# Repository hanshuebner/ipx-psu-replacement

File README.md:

# Sun SPARCstation IPC/IPX replacement power supply

I've got tired of unsuccessfully trying to repair the APS-02 power
supply that is built into Sun's SPARCstation IPC and IPX workstations,
so I designed this replacement.  It uses two encapsulated power
supplies and a MAX8215 power supply monitoring chip to generate the
SENS signal.

Here's a picture of my version 1 build.  It has the base load
resistors bodged on.  The layout has been revised since:

Several parts out of the original PSU board are reused and need to be
desoldered:

|Ref |Qnty|Value    |Notes                                         |
|----|----|---------|----------------------------------------------|
|F1  |1   |3.15A T  |Fuse + fuse holder                            |
|J1  |1   |L        |Power input (3 pin, middle pin not connected) |
|J2  |1   |AC IN    |Power from IEC input (1 pin)                  |
|J5  |1   |AC OUT   |Power to IEC output (1 pin)                   |
|J12 |1   |Fan      |Power to fan (2 pin)                          |
|K1  |1   |DH2U TV3 |IEC output relay                              |
|    |1   |         |Cable harness including floppy connector      |

Another couple of parts need to be bought

|Ref           |Qnty|Value      |Description                                                                 |
|--------------|----|-----------|----------------------------------------------------------------------------|
|U1            |1   |74HCT11D   |Triple 3-input AND, SO-14                                                   |
|U2            |1   |MAX8215CSD |Voltage Monitor IC, SO-14                                                   |
|D1            |1   |PMEG2010ER |20V 1A Planar Schottky barrier rectifier, SOD-123                           |
|C1, C2        |2   |100nF      |Capacitor bipolar SMD 0603                                                  |
|C3            |1   |1µF        |Capacitor bipolar SMD 0603                                                  |
|R1, R2, R3, R4|4   |680kΩ      |Resistor SMD 0603                                                           |
|R5, R6        |2   |120Ω       |Resistor radial 5W, 20mmx9mmx9mm, 25mm pitch                                |
|PS1           |1   |IRM-60-5   |MeanWell IRM-60-5 50 Watt AC/DC power supply, 5V, 10A                       |
|PS2           |1   |RACM30-12DK|RECOM RACM30-12DK/277 30 Watt Dual Output AC/DC power supply, ±12V, ±1250mA |

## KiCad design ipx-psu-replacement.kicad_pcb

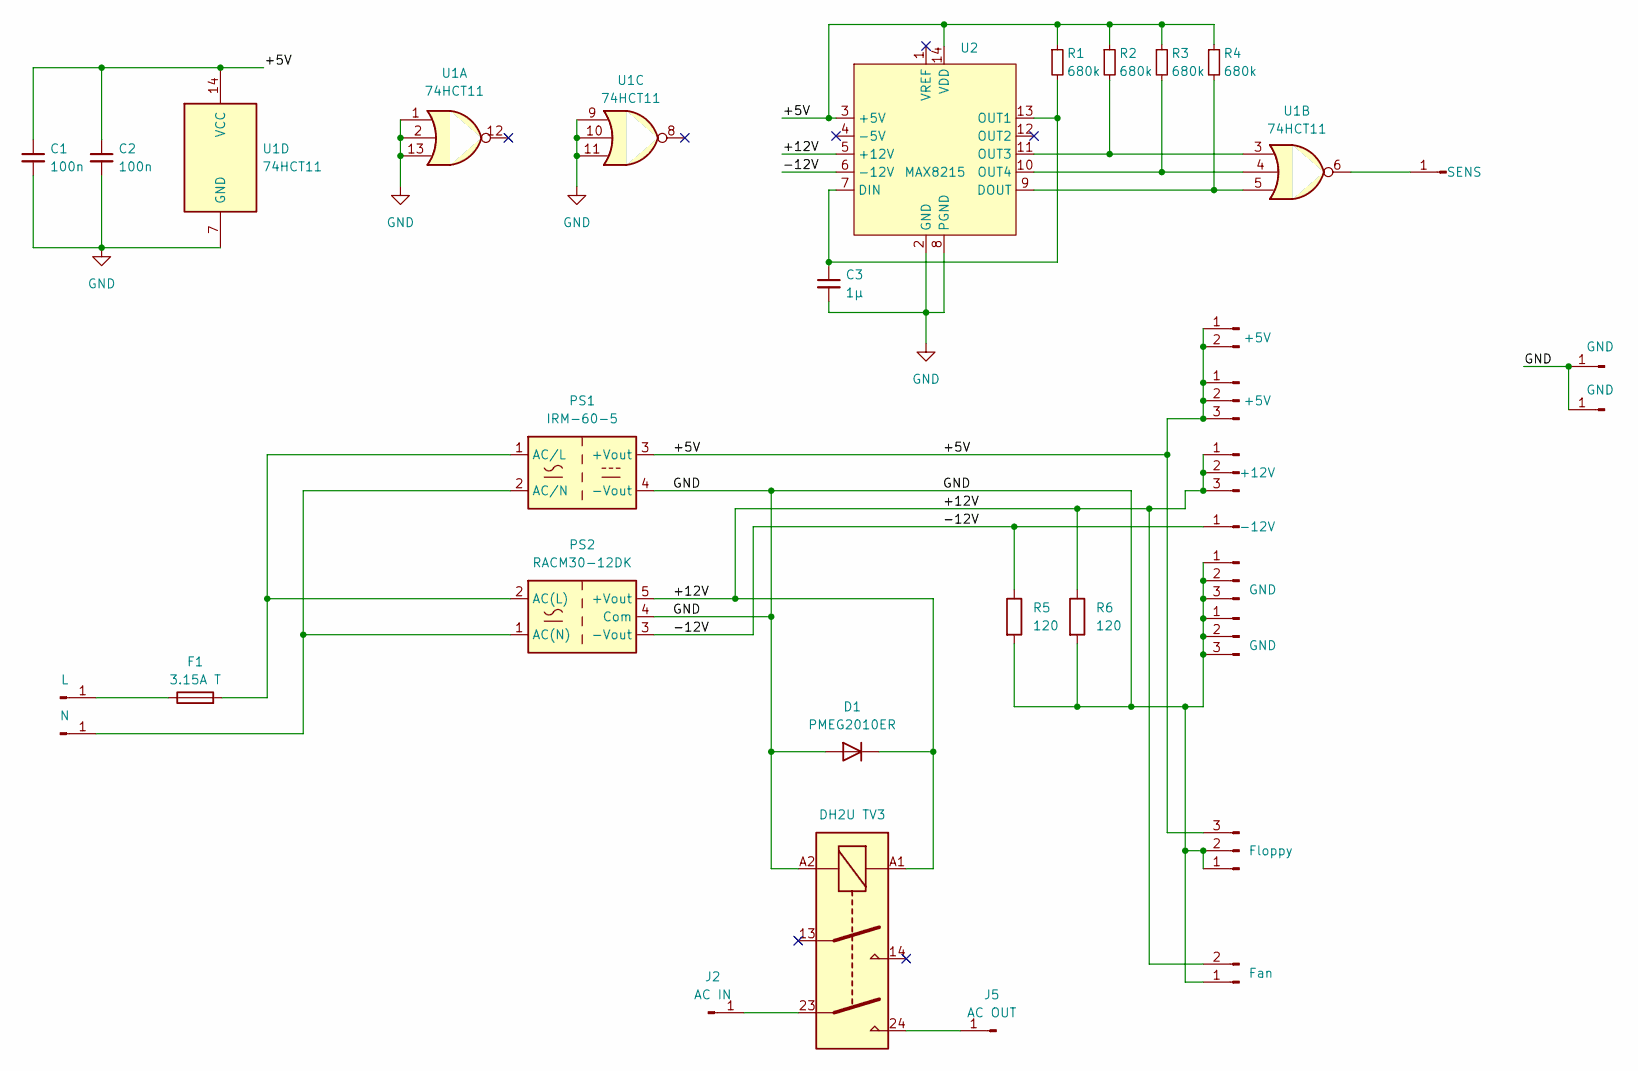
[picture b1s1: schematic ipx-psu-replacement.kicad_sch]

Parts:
C1, C2: 100n; C_0603_1608Metric_Pad1.08x0.95mm_HandSolder
C3: 1µ; C_0603_1608Metric_Pad1.08x0.95mm_HandSolder
D1: PMEG2010ER; D_SOD-123
F1: 3.15A T; Fuseholder_Clip-5x20mm_Littelfuse_111_Inline_P20.00x5.00mm_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
J1: L; SolderWire-1.5sqmm_1x01_D1.7mm_OD3mm
J2: AC IN; SolderWire-1.5sqmm_1x01_D1.7mm_OD3mm
J3, J11: GND; SolderWire-1.5sqmm_1x03_P6mm_D1.7mm_OD3mm
J4: Floppy; PinHeader_1x03_P2.54mm_Vertical
J5: AC OUT; SolderWire-1.5sqmm_1x01_D1.7mm_OD3mm
J6: N; SolderWire-1.5sqmm_1x01_D1.7mm_OD3mm
J7: +12V; SolderWire-1.5sqmm_1x03_P6mm_D1.7mm_OD3mm
J8: +5V; SolderWire-1.5sqmm_1x02_P6mm_D1.7mm_OD3mm
J9: +5V; SolderWire-1.5sqmm_1x03_P6mm_D1.7mm_OD3mm
J10: -12V; SolderWire-1.5sqmm_1x01_D1.7mm_OD3mm
J12: Fan; PinHeader_1x02_P2.54mm_Vertical
J13: SENS; SolderWire-1.5sqmm_1x01_D1.7mm_OD3mm
J14, J15: GND; SolderWire-2sqmm_1x01_D2mm_OD3.9mm
K1: DH2U TV3; Relay_DPST_Omron_G2RL-2A
PS1: IRM-60-5; Converter_ACDC_MeanWell_IRM-60-xx_THT
PS2: RACM30-12DK; CONV_RACM30-24SK_277
R1, R2, R3, R4: 680k; R_0603_1608Metric_Pad0.98x0.95mm_HandSolder
R5, R6: 120; R_Axial_DIN0922_L20.0mm_D9.0mm_P25.40mm_Horizontal
U1: 74HCT11; SO-14_3.9x8.65mm_P1.27mm
U2: MAX8215; SO-14_3.9x8.65mm_P1.27mm

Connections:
/+5V: C1.1, C2.1, J4.3, J8.1, J8.2, J9.1, J9.2, J9.3, PS1.3 (+Vout), R1.1, R2.1, R3.1, R4.1, U1.14 (VCC), U2.3 (+5V), U2.14 (VDD)
/+12V: D1.1 (K), J7.1, J7.2, J7.3, J12.2, K1.A1, PS2.5 (+Vout), R6.1, U2.5 (+12V)
/-12V: J10.1, PS2.3 (-Vout), R5.1, U2.6 (-12V)
GND: C1.2, C2.2, C3.2, D1.2 (A), J3.1, J3.2, J3.3, J4.1, J4.2, J11.1, J11.2, J11.3, J12.1, J14.1, J15.1, K1.A2, PS1.4 (-Vout), PS2.4 (Com), R5.2, R6.2, U1.1, U1.2, U1.7 (GND), U1.9, U1.10, U1.11, U1.13, U2.2 (GND), U2.8 (PGND)
unnamed: F1.1, J1.1
unnamed: J2.1, K1.23
unnamed: J5.1, K1.24
unnamed: J6.1, PS1.2 (AC/N), PS2.1 (AC(N))
unnamed: J13.1, U1.6
unnamed: F1.2, PS1.1 (AC/L), PS2.2 (AC(L))
unnamed: C3.1, R1.2, U2.7 (DIN), U2.13 (OUT1)
unnamed: R4.2, U1.5, U2.9 (DOUT)
unnamed: R2.2, U1.3, U2.11 (OUT3)
unnamed: R3.2, U1.4, U2.10 (OUT4)

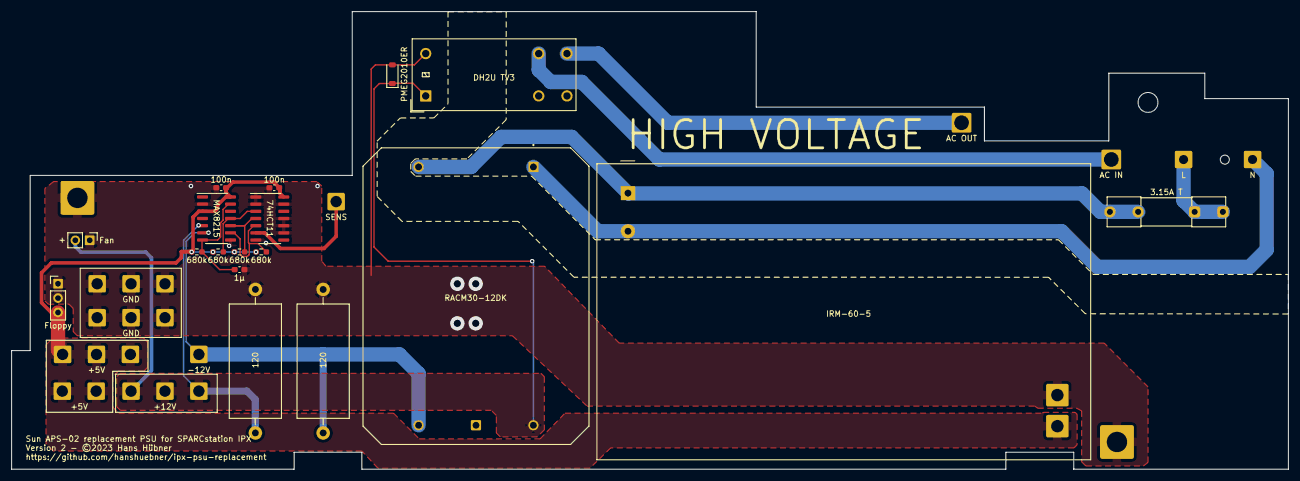
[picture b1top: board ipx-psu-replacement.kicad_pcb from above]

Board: 2 copper layers, 226.0 x 81.0 mm, 31 parts (0 on the bottom side), 14 nets.

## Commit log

2023-10-12 add power good sensing
2023-10-12 supervisor circuitry fixed & improved
2023-10-12 more adjustments
2023-10-12 v1 - sent to production
2023-10-31 add base load resistors
2023-11-01 hct27 -> hct11
2023-11-01 README with BOM and pictures
2023-11-01 correct mounting hole locations
2023-12-19 fix part number for +-12V supply
2023-12-19 fix datasheet link
2024-08-31 gerbers updated
2025-05-08 Fix U1 schematic symbol and flyback diode description

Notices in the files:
ipx-psu-replacement.kicad_pcb:
Version 2 - ©2023 Hans Hübner
